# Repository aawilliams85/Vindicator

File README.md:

SteamVR Saber Staff based on Tundra Labs sample project here: https://github.com/tundra-labs/rp2040_examples

## Structure
The subfolders in the main directory are as follows:
* VindicatorDriver
    * This contains the driver that tells SteamVR how to use the controller.
    * The subfolder "vindicator" should be copied to "C:\Program Files (x86)\Steam\steamapps\common\SteamVR\drivers"
* VindicatorFirmware
    * This is the RP2040 Arduino code that is programmed into the dev board
* VindicatorInputPCB
    * This is the KiCAD design for the button input board that connects to the RP2040 dev board.
* VindicatorJson
    * This contains example before and after device JSON files to show how to convert to/from the stock Tundra Tracker configuration. 
* VindicatorMechanical
    * This is the FreeCAD model for the 3D printed parts.

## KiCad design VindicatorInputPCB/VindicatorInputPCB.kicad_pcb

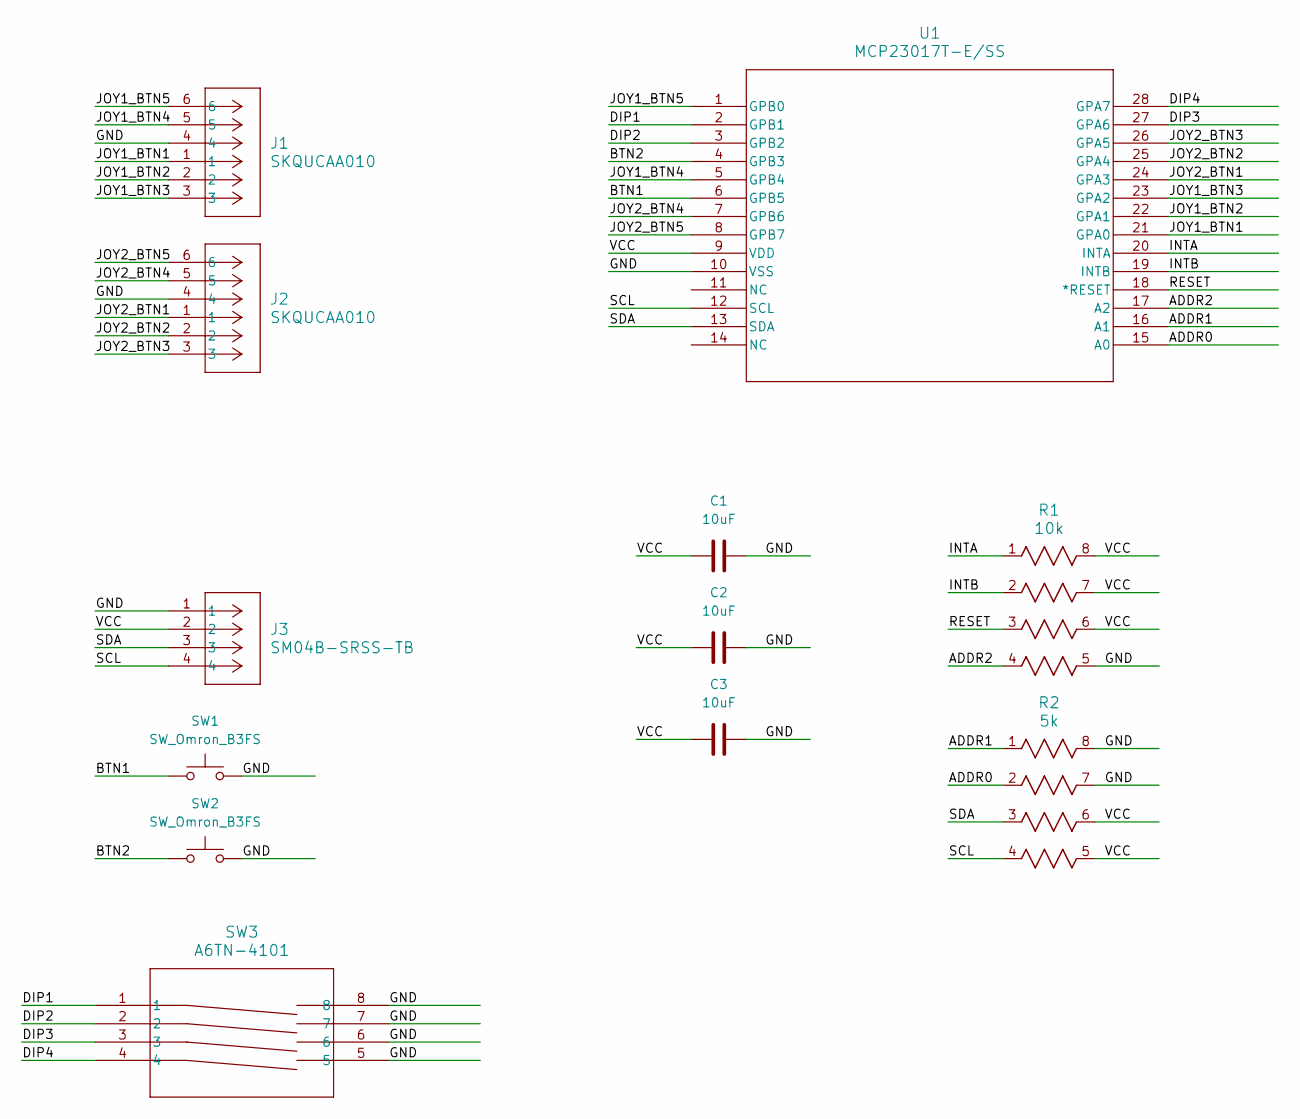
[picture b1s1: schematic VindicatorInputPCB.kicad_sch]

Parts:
C1, C2, C3: 10uF; C_1206_3216Metric
J1, J2: SKQUCAA010; CONN_SKQUC_ALPS
J3: SM04B-SRSS-TB; CONN_SM04B-SRSS-TB_JST
R1: 10k; EXBV8V_PAN
R2: 5k; EXBV8V_PAN
SW1, SW2: SW_Omron_B3FS; SW_TH_Tactile_Omron_B3F-10xx
SW3: A6TN-4101; SW_A6TN-4101_OMR
U1: MCP23017T-E/SS; SSOP28_MC_MCH

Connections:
/ADDR0: R2.2, U1.15 (A0)
/ADDR1: R2.1, U1.16 (A1)
/ADDR2: R1.4, U1.17 (A2)
/BTN1: SW1.1, U1.6 (GPB5)
/BTN2: SW2.1, U1.4 (GPB3)
/DIP1: SW3.1, U1.2 (GPB1)
/DIP2: SW3.2, U1.3 (GPB2)
/DIP3: SW3.3, U1.27 (GPA6)
/DIP4: SW3.4, U1.28 (GPA7)
/GND: C1.2, C2.2, C3.2, J1.4, J2.4, J3.1, R1.5, R2.7, R2.8, SW1.2, SW2.2, SW3.5, SW3.6, SW3.7, SW3.8, U1.10 (VSS)
/INTA: R1.1, U1.20 (INTA)
/INTB: R1.2, U1.19 (INTB)
/JOY1_BTN1: J1.1, U1.21 (GPA0)
/JOY1_BTN2: J1.2, U1.22 (GPA1)
/JOY1_BTN3: J1.3, U1.23 (GPA2)
/JOY1_BTN4: J1.5, U1.5 (GPB4)
/JOY1_BTN5: J1.6, U1.1 (GPB0)
/JOY2_BTN1: J2.1, U1.24 (GPA3)
/JOY2_BTN2: J2.2, U1.25 (GPA4)
/JOY2_BTN3: J2.3, U1.26 (GPA5)
/JOY2_BTN4: J2.5, U1.7 (GPB6)
/JOY2_BTN5: J2.6, U1.8 (GPB7)
/RESET: R1.3, U1.18 (*RESET)
/SCL: J3.4, R2.4, U1.12 (SCL)
/SDA: J3.3, R2.3, U1.13 (SDA)
/VCC: C1.1, C2.1, C3.1, J3.2, R1.6, R1.7, R1.8, R2.5, R2.6, U1.9 (VDD)

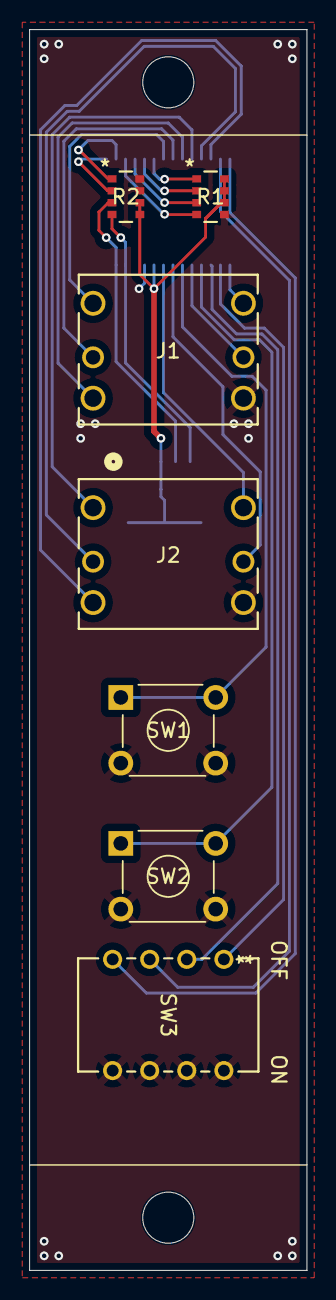
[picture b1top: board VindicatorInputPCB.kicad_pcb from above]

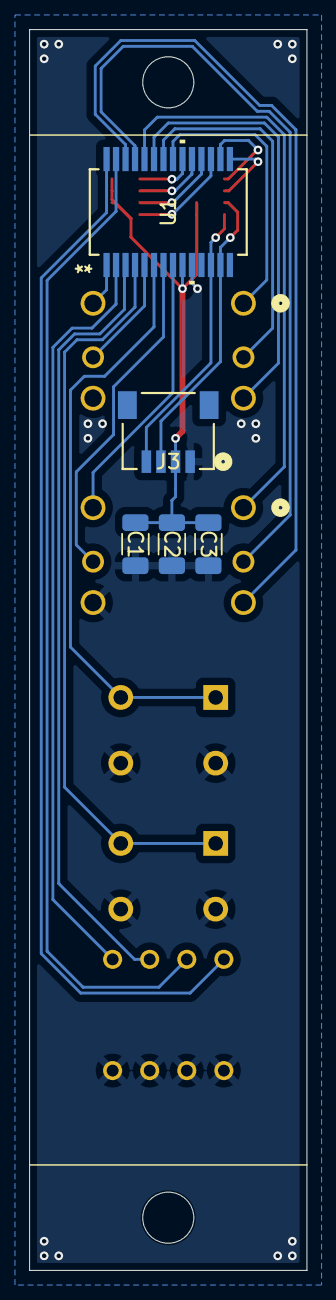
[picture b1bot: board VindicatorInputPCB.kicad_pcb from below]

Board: 2 copper layers, 19.0 x 85.0 mm, 12 parts (5 on the bottom side), 26 nets.

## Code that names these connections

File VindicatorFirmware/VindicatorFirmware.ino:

#include <Adafruit_MCP23X17.h>
#include "tundra_mapped_input.h"

#define RP2040_BB_LED           (25)

/////////////////////////////////////////////////////////////////////
// I/O Expander Pinout
/////////////////////////////////////////////////////////////////////
#define JOY1_BTN1_PIN 0    # GPA0 / 21
#define JOY1_BTN2_PIN 1    # GPA1 / 22
#define JOY1_BTN3_PIN 2    # GPA2 / 23
#define JOY1_BTN4_PIN 12   # GPB4 / 5
#define JOY1_BTN5_PIN 8    # GPB0 / 1

#define JOY2_BTN1_PIN 3    # GPA3 / 24
#define JOY2_BTN2_PIN 4    # GPA4 / 25
#define JOY2_BTN3_PIN 5    # GPA5 / 26
#define JOY2_BTN4_PIN 14   # GPB6 / 7
#define JOY2_BTN5_PIN 15   # GPB7 / 8

#define BTN1_PIN 13        # GPB5 / 6
#define BTN2_PIN 11        # GPB3 / 4

#define DIP1_PIN 9         # GPB1 / 2
#define DIP2_PIN 10        # GPB2 / 3
#define DIP3_PIN 6         # GPA6 / 27
#define DIP4_PIN 7         # GPA7 / 28

Adafruit_MCP23X17 mcp;
/////////////////////////////////////////////////////////////////////


// Create TMI object to communicate with Tundra Tracker
TMI tundra_tracker;
void csn_irq( uint gpio, uint32_t event_mask );  // Chip select IRQ must be top level so let's make one and connect it later in setup

// Use packed structs to define the inputs for your controller
// First we make a struct of buttons
typedef struct __attribute__( ( packed, aligned( 1 ) ) )
{

}
controller_buttons_t;

// Make a top level struct that packs the button data along with the rest of the controller analog values
typedef struct __attribute__( ( packed, aligned( 1 ) ) )
{
  uint16_t      buttons         : 16;
} 
controller_data_t;

// declare the controller struct for use
controller_data_t controller_data;

uint16_t input_data = 0; // I/O data from this scan
uint16_t input_data_last = 0; // I/O data from the previous scan
uint32_t interval_gpio = 25; // Time interval to check GPIO for new data (ms)
uint32_t next_time_gpio = 0;

uint32_t interval_send = 1000; // Time interval to send data to tracker, even if no data has changed (ms)
uint32_t next_time_send = 0;
bool send_requested = false;
bool led_state = false;

void setup() {
  
  pinMode(RP2040_BB_LED, OUTPUT);

  // init the communication to Tundra Tracker, setup the CS irq callback (this has to be at Top level in arduino it seems)
  tundra_tracker.init( );
  gpio_set_irq_enabled_with_callback( tundra_tracker.get_cs_pin(), GPIO_IRQ_EDGE_RISE | GPIO_IRQ_EDGE_FALL, true, &csn_irq );

  Serial.begin();
  delay(1000);
  //while(!Serial){} //Debug operation only
  while (!mcp.begin_I2C(0x20, &Wire1)){
    Serial.println("Waiting for i2c");
    delay(250);
  }
  for (int i = 0; i < 16; i++){
    mcp.pinMode(i, INPUT_PULLUP);
  }
}


// the loop function runs over and over again forever
void loop() {
  if (millis() > next_time_gpio) {
    input_data = ~mcp.readGPIOAB();
    //Serial.println(input_data);
    next_time_gpio = millis() + interval_gpio;
  }

  if ((millis() > next_time_send)||(input_data != input_data_last)) {
    controller_data.buttons = input_data;
    send_requested = true;
    next_time_send = millis() + interval_send;
  }

  if (send_requested) {
    if (tundra_tracker.data_ready()){
      tundra_tracker.send_data(&controller_data, sizeof(controller_data));
      tundra_tracker.handle_rx_data();
      digitalWrite(RP2040_BB_LED, led_state ^= true);
      input_data_last = input_data;
      send_requested = false;
    }
  }
}

// Callback for SPI Chipselect, just connect in the tmi irq function
void csn_irq( uint gpio, uint32_t event_mask )
{
  tundra_tracker.csn_irq( gpio, event_mask );
}

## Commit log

2024-06-22 Initial rev
2024-06-22 Fixed I/O getting stuck
